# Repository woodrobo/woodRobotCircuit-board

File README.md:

# woodRobotCircuit-board
趣味でロボコン的なロボットを動かす回路を作ろうプロジェクト（？）の回路・基板リポジトリである。ファームウェアは[ここ](https://github.com/woodrobo/woodRobotCircuit-firmware/tree/kanojo_robo)。
ロボコンや趣味のロボット製作等の参考にどうぞ。  

メインボードとモータードライバは2MbpsのRS485で接続されており、プロトコルはwoodRS485という独自規格を用いているが、これも[リポジトリ](https://github.com/woodrobo/wood_rs485)として公開されており、C言語が使用できるマイコンであればどのマイコンでも移植できるよう実装されている。  
モータードライバーは電流制御に対応しており高度な制御が可能となる。  

# 電流制御とは
モーターは一般に抵抗とコイル、そして回転速度に比例する逆起電力の3つが直列接続されたモデルで表現されます。  

$$ Vin = Ri + L\frac{di}{dt}+V$$

電子工作でよく使用されるPWM制御ではこの3つの要素全体にかける電圧を制御しているのでこれは直接的に物理的な意味を持ちません。モーターに流れる電流はトルクに比例すると言われこの電流を制御する電流制御方式ではトルクという物理量を直接的に扱うことができます。

$$ \tau = K_t i $$

製品や研究の世界ではこのトルク制御により運動方程式からモデルを立てて制御をすることが一般となっています。例えばロボティクスでは動力学や逆動力学によりロボットアームを制御しています。モデルに基づいた制御をするために電流制御は必須の機能です。

# 基板の簡単な紹介
woodBoard  
メインボードでありRS485以外にもSPI,I2C,UART,CANなどの通信ポートを備えている。また余った全てのGPIOをピンソケットに出しており、3MbpsのADCモジュールが6つ搭載されているため合計で18Mspsもの高速なAD変換を実現できる。もちろんこれはモジュール数であるのでAD変換可能なピン数はこれより多い。

woodTerminal  
モータードライバー基板などをまとめるための基板であり、1つのターミナル基板につきモータードライバー基板を5枚配置することができる。制御側の電源はRS485ポートの5V電源のほか、DCDCコンバータが搭載されているのでLiPo 3S(11.1V)等からも5Vを生成できる。
  
woodCurrentMD  
初期のモータードライバーであるが、ゲートドライバICが手に入らなかったことや回路トラブルにより闇の基板だぞ。

woodCurrentMD2  
20kHz電流制御モータードライバー。ロジック側とパワー側はフォトカプラで絶縁されており、モーター電流は磁気式の電流センサで計測している。UARTポート、エンコーダポート、ADCポートを搭載しており、また搭載しているマイコンはマルチプレクサにより自由にピン配置を変更できるため拡張性に優れる。180MHz/200MHzデュアルコアマイコンdsPIC33CHにより電流制御とその他処理をコアで分離するためプログラムの拡張性に優れる。  

# 基板発売について  
ここのサイトで基板のみを売ってるぞ！  
https://woodrobo.booth.pm/items/4136212

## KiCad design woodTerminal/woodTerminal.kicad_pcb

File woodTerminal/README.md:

# woodTerminal
モータードライバーなどを5枚までまとめるターミナル基板

仕様
- ロジック側
	- RS485の4ピンポート(A,B,5V,GND)
		- RS485の終端抵抗は横にあるピンヘッダをショートすることで行う
	- 外部電源供給
		- LiPo3S(11.1V)などからDCDCコンバータを通して5Vを供給する(オプション)
	- 電源選択は基板裏面にあるパッドをショートして行う(4ピンコネクタor外部供給)
	- よく考えると外部供給は一度も試してない(ｶｽ)
- パワー側
	- Tコネクタ
  
  # 部品について  
  部品表.csvおよび部品個数表.csvを見てくれ。

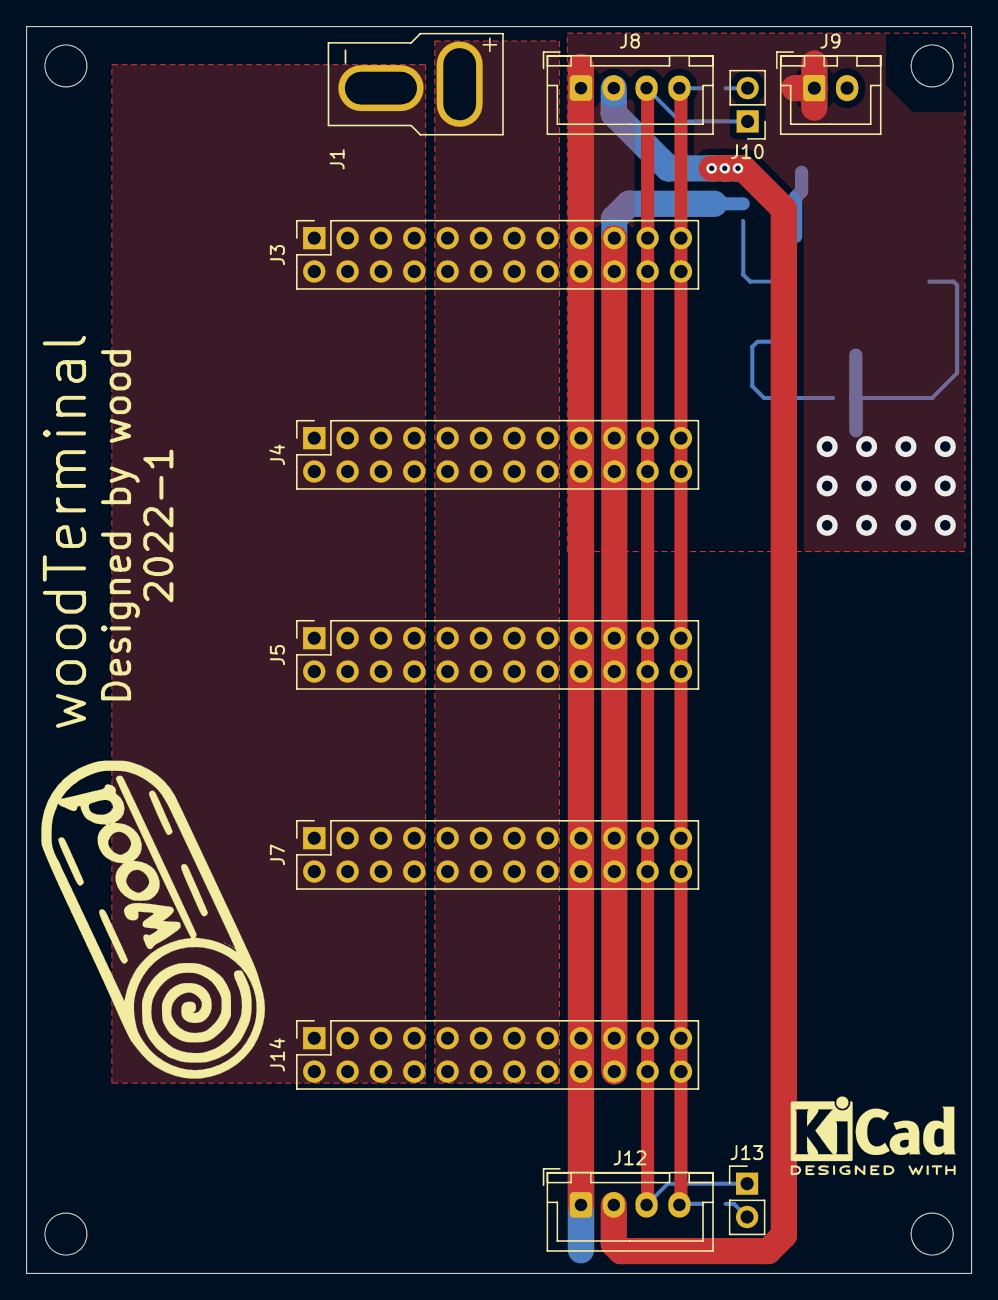
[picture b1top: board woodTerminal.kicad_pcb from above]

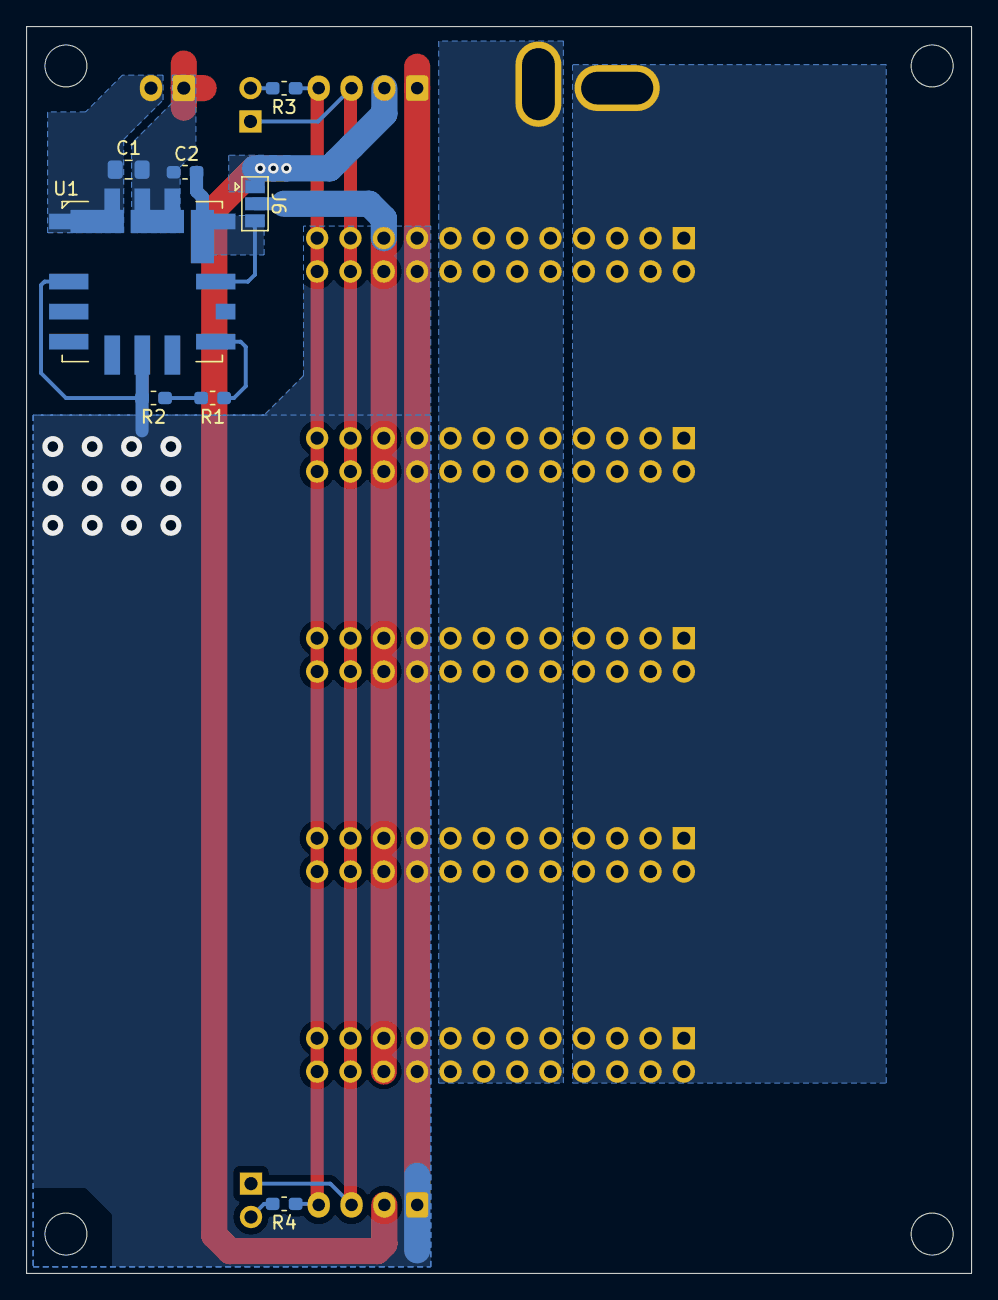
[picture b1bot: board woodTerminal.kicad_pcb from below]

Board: 2 copper layers, 72.0 x 95.0 mm, 23 parts (8 on the bottom side), 13 nets.

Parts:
 : MountingHole_3.2mm_M3
 #2,  #3,  #4: MountingHole_3.2mm_M3
C1: 22u; C_0805_2012Metric_Pad1.15x1.40mm_HandSolder
C2: 10u; C_0603_1608Metric_Pad1.05x0.95mm_HandSolder
J1: Conn_01x02; DeansTConnector_Male
J3, J4, J5, J7, J14: Conn_02x12_Odd_Even; PinSocket_2x12_P2.54mm_Vertical
J6: Conn_01x03; SolderJumper-3_P1.3mm_Open_Pad1.0x1.5mm
J8, J12: Conn_01x04; JST_XH_B4B-XH-A_1x04_P2.50mm_Vertical
J9: Conn_01x02; JST_XH_B2B-XH-A_1x02_P2.50mm_Vertical
J10, J13: Conn_01x02; PinHeader_1x02_P2.54mm_Vertical
R1: 1k; R_0603_1608Metric_Pad1.05x0.95mm_HandSolder
R2: 330; R_0603_1608Metric_Pad1.05x0.95mm_HandSolder
R3, R4: 120; R_0603_1608Metric_Pad1.05x0.95mm_HandSolder
U1: DCDC_Converter_OKL

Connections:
+5V: J3.19, J3.20, J4.19, J4.20, J5.19, J5.20, J6.2, J7.19, J7.20, J14.19, J14.20
+BATT: J1.2, J3.9, J3.10, J3.11, J3.12, J3.13, J3.14, J3.15, J3.16, J4.9, J4.10, J4.11, J4.12, J4.13, J4.14, J4.15, J4.16, J5.9, J5.10, J5.11, J5.12, J5.13, J5.14, J5.15, J5.16, J7.9, J7.10, J7.11, J7.12, J7.13, J7.14, J7.15, J7.16, J14.9, J14.10, J14.11, J14.12, J14.13, J14.14, J14.15, J14.16
/DCDC_OUT: C2.1, J6.3, U1.4, U1.5
/RS485_5V: J6.1, J8.2, J12.2
/RS485_A: J3.23, J3.24, J4.23, J4.24, J5.23, J5.24, J7.23, J7.24, J8.4, J12.4, J14.23, J14.24, R3.1, R4.1
/RS485_B: J3.21, J3.22, J4.21, J4.22, J5.21, J5.22, J7.21, J7.22, J8.3, J10.1, J12.3, J13.1, J14.21, J14.22
GND: C1.2, C2.2, J3.17, J3.18, J4.17, J4.18, J5.17, J5.18, J7.17, J7.18, J8.1, J9.1, J12.1, J14.17, J14.18, R2.2, U1.1, U1.3, U1.7
GNDPWR: J1.1, J3.1, J3.2, J3.3, J3.4, J3.5, J3.6, J3.7, J3.8, J4.1, J4.2, J4.3, J4.4, J4.5, J4.6, J4.7, J4.8, J5.1, J5.2, J5.3, J5.4, J5.5, J5.6, J5.7, J5.8, J7.1, J7.2, J7.3, J7.4, J7.5, J7.6, J7.7, J7.8, J14.1, J14.2, J14.3, J14.4, J14.5, J14.6, J14.7, J14.8
unnamed: J10.2, R3.2
unnamed: J13.2, R4.2
unnamed: R1.1, U1.6
unnamed: R1.2, R2.1
VCC: C1.1, J9.2, U1.2

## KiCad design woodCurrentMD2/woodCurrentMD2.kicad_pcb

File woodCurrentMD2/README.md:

# woodCurrentMD2
2Mbps RS485対応電流制御DCモータードライバー

仕様
- 通信規格2Mbps RS485
	- 受信：電圧制御(PWM値)、電流制御
	- 送信：電流値、AD変換ポートの値、エンコーダのカウント値
- woodTerminal接続端子
	- ロジック側とパワー側は絶縁されている
	- ロジック側：A, B, 5V, GND
	- パワー側　：VCC, GND
	- 詳細はwoodTerminalを参照の事
- 20kHz電流制御
- デバッグUARTポート
	- 現状RXから信号が出てる()
- インクリメンタル型エンコーダポート
	- PICのQEI機能でハードウェア処理
	- たぶん高速な波形も読める
	- Z相はファームウェアが現在対応してない、配線しないこと
- (ポテンショなどの)AD変換ポート

通信規格  
woodRS485で以下のデータをやり取りする。

**マイコンボード→モータードライバー**  
モードは0で電圧制御(PWM値)、1で電流制御を意味する。16bit値は16bitのsigned int型であり、電圧制御ではPWM値(-10000 ~ 10000)を指示し、電流制御では1当たり0.0179[A]となる。  
例えば、電圧制御PWM1000ならば「0,3,232」となる。電流制御1Aならば「1,0,56」(1.0024A)となる。

| バイト数 | データ |
----|---- 
| 1 | モード |
| 2 | 16bit値(上位バイト) |
| 3 | 16bit値(下位バイト) |

**モータードライバー→マイコンボード**  
電流値は16bitのsigned int型であり、1あたり0.0179[A]を意味する。AD変換ポートはAD変換値(12bit 0-4095)が入っている。 エンコーダは16bitのsigned int型である。(インクリメンタル型エンコーダは差分しか意味を持たないのでunsignedと解釈してもsignedと解釈しても同じ)

| バイト数 | データ |
----|---- 
| 1 | 電流値(上位バイト) |
| 2 | 電流値(下位バイト) |
| 3 | AD変換ポート(上位バイト) |
| 4 | AD変換ポート(下位バイト) |
| 5 | エンコーダ(上位バイト) |
| 6 | エンコーダ(下位バイト) |
  
  # 部品について  
  部品表.csvおよび部品個数表.csvを見てくれ。

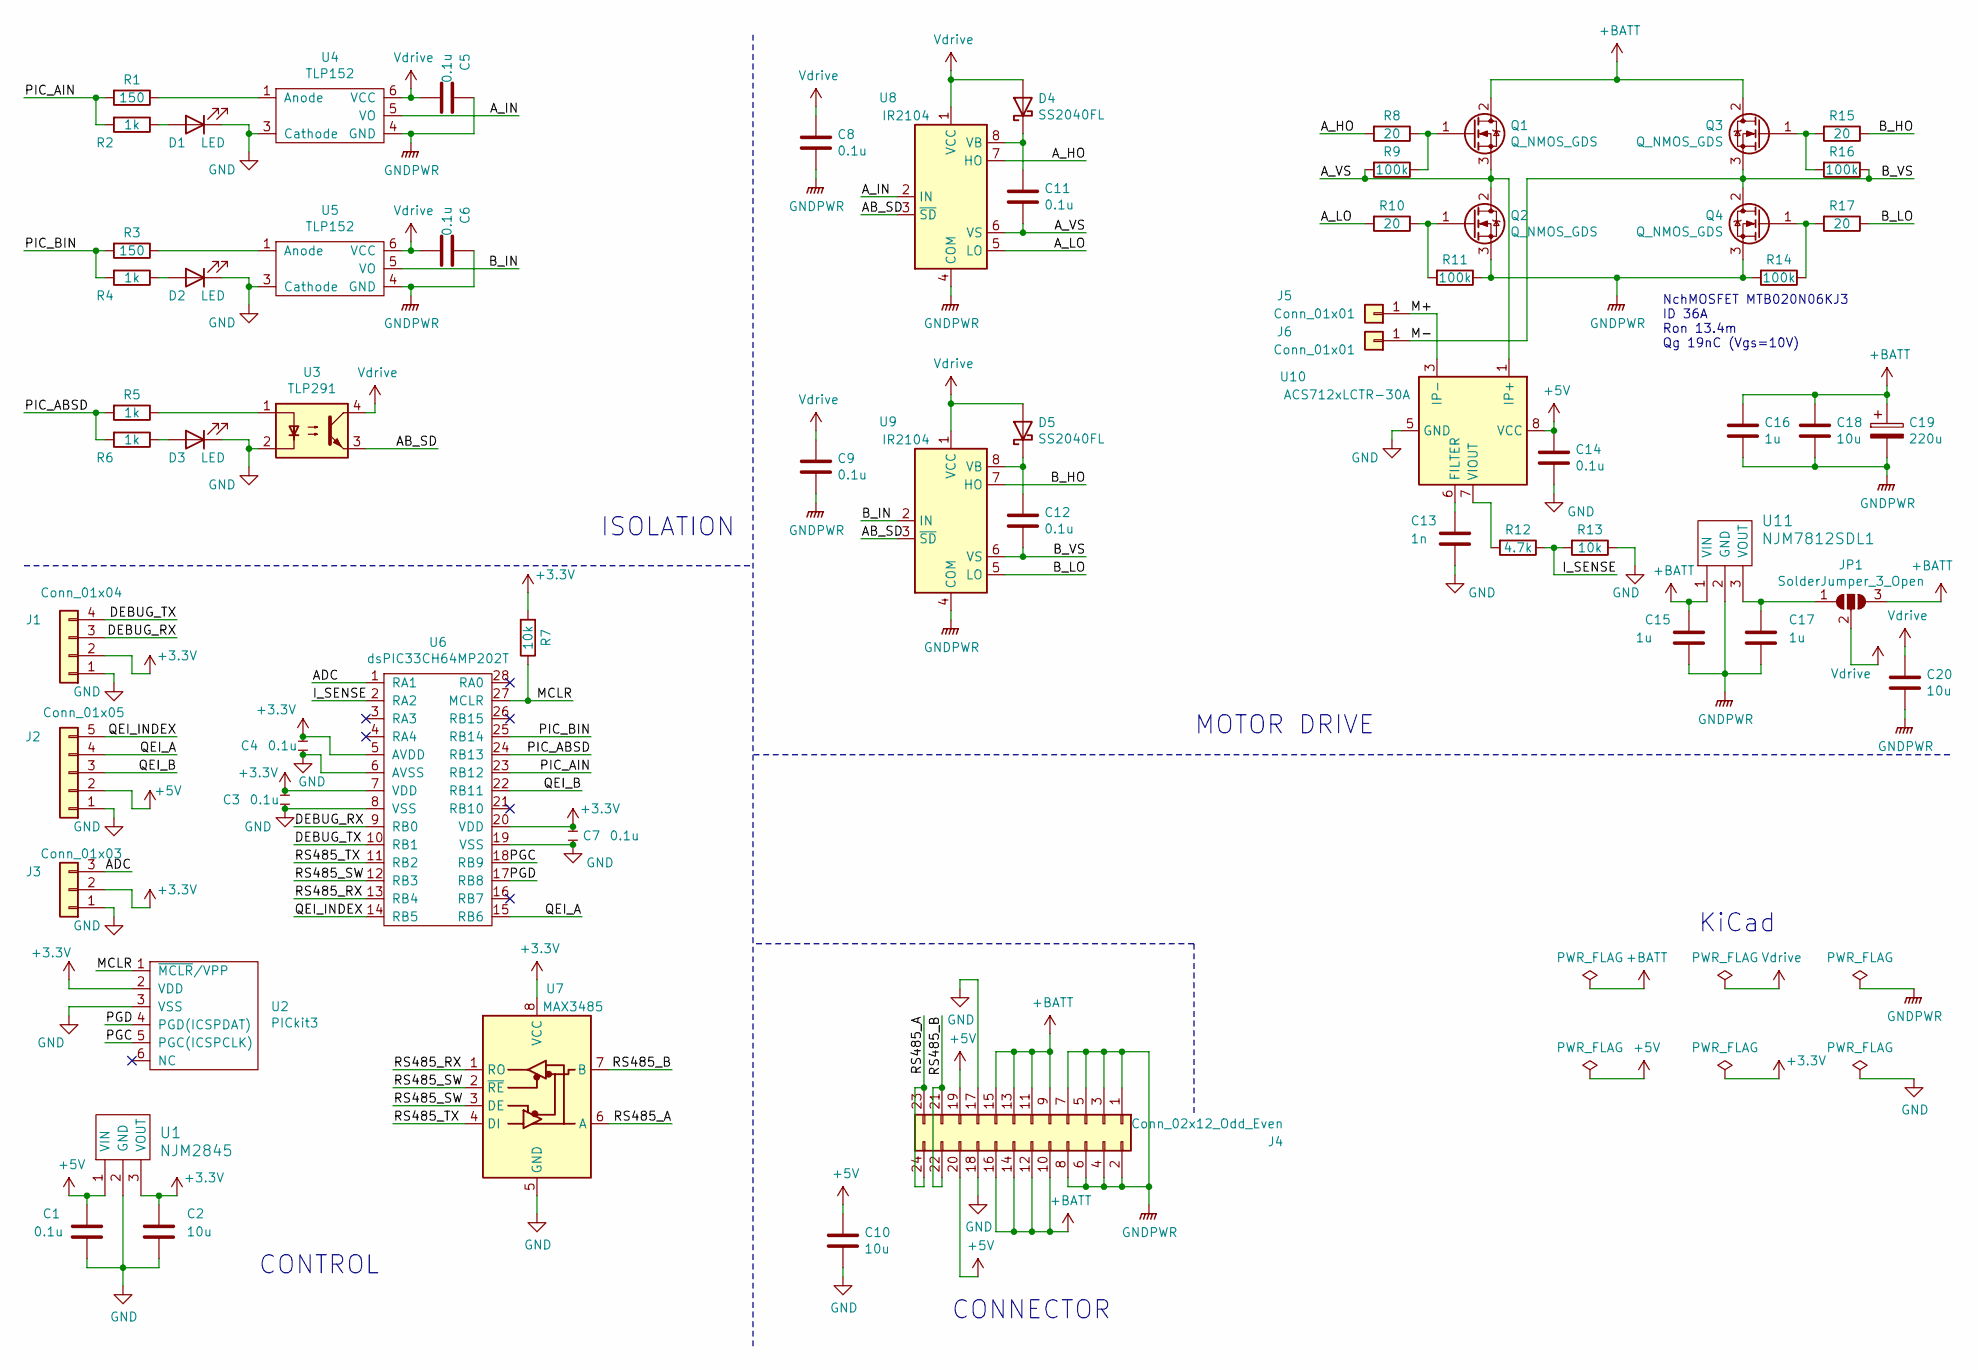
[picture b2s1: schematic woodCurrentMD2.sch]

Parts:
C1, C3, C4, C5, C6, C7, C8, C9, C11, C12, C14: 0.1u; C_0603_1608Metric
C2, C10, C18, C20: 10u; C_0603_1608Metric
C13: 1n; C_0603_1608Metric
C15, C16, C17: 1u; C_0603_1608Metric
C19: 220u; CP_Elec_10x10
D1, D2, D3: LED; LED_0603_1608Metric
D4, D5: SS2040FL; D_1206_3216Metric
J1: Conn_01x04; JST_XH_S4B-XH-A_1x04_P2.50mm_Horizontal
J2: Conn_01x05; JST_XH_S5B-XH-A_1x05_P2.50mm_Horizontal
J3: Conn_01x03; JST_XH_S3B-XH-A_1x03_P2.50mm_Horizontal
J4: Conn_02x12_Odd_Even; PinHeader_2x12_P2.54mm_Vertical
J5, J6: Conn_01x01; MountingHole_2.2mm_M2_Pad
JP1: SolderJumper_3_Open; SolderJumper-3_P1.3mm_Open_RoundedPad1.0x1.5mm_NumberLabels
Q1, Q2, Q3, Q4: Q_NMOS_GDS; TO-252-2
R1, R3: 150; R_0603_1608Metric
R2, R4, R5, R6: 1k; R_0603_1608Metric
R7, R13: 10k; R_0603_1608Metric
R8, R10, R15, R17: 20; R_0603_1608Metric
R9, R11, R14, R16: 100k; R_0603_1608Metric
R12: 4.7k; R_0603_1608Metric
U1: NJM2845; TO-252-2
U2: PICkit3; PinHeader_1x06_P2.54mm_Horizontal
U3: TLP291; SOIC-4_4.55x2.6mm_P1.27mm
U4, U5: TLP152; SO-6_4.4x3.6mm_P1.27mm
U6: dsPIC33CH64MP202T; SSOP-28_5.3x10.2mm_P0.65mm
U7: MAX3485; SOIC-8_3.9x4.9mm_P1.27mm
U8, U9: IR2104; SOIC-8_3.9x4.9mm_P1.27mm
U10: ACS712xLCTR-30A; SOIC-8_3.9x4.9mm_P1.27mm
U11: NJM7812SDL1; TO-252-2

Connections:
+3V3: C2.1, C3.1, C4.1, C7.1, J1.2, J3.2, R7.2, U1.3 (VOUT), U2.2 (VDD), U6.5 (AVDD), U6.7 (VDD), U6.20 (VDD), U7.8 (VCC)
+5V: C1.1, C10.1, C14.1, J2.2, J4.19, J4.20, U1.1 (VIN), U10.8 (VCC)
+BATT: C15.1, C16.1, C18.1, C19.1, J4.9, J4.10, J4.11, J4.12, J4.13, J4.14, J4.15, J4.16, JP1.3 (B), Q1.2 (D), Q3.2 (D), U11.1 (VIN)
/AB_SD: U3.3, U8.3 (~SD), U9.3 (~SD)
/ADC: J3.3, U6.1 (RA1)
/A_HO: R8.2, U8.7 (HO)
/A_IN: U4.5 (VO), U8.2 (IN)
/A_LO: R10.2, U8.5 (LO)
/A_VS: C11.2, Q1.3 (S), Q2.2 (D), R9.2, U8.6 (VS), U10.1 (IP+), U10.2 (IP+)
/B_HO: R15.1, U9.7 (HO)
/B_IN: U5.5 (VO), U9.2 (IN)
/B_LO: R17.1, U9.5 (LO)
/B_VS: C12.2, J6.1, Q3.3 (S), Q4.2 (D), R16.1, U9.6 (VS)
/DEBUG_RX: J1.3, U6.9 (RB0)
/DEBUG_TX: J1.4, U6.10 (RB1)
/I_SENSE: R12.1, R13.2, U6.2 (RA2)
/M+: J5.1, U10.3 (IP-), U10.4 (IP-)
/MCLR: R7.1, U2.1 (~MCLR~/VPP), U6.27 (MCLR)
/PGC: U2.5 (PGC(ICSPCLK)), U6.18 (RB9)
/PGD: U2.4 (PGD(ICSPDAT)), U6.17 (RB8)
/PIC_ABSD: R5.2, R6.2, U6.24 (RB13)
/PIC_AIN: R1.2, R2.2, U6.23 (RB12)
/PIC_BIN: R3.2, R4.2, U6.25 (RB14)
/QEI_A: J2.4, U6.15 (RB6)
/QEI_B: J2.3, U6.22 (RB11)
/QEI_INDEX: J2.5, U6.14 (RB5)
/RS485_A: J4.23, J4.24, U7.6 (A)
/RS485_B: J4.21, J4.22, U7.7 (B)
/RS485_RX: U6.13 (RB4), U7.1 (RO)
/RS485_SW: U6.12 (RB3), U7.2 (~RE), U7.3 (DE)
/RS485_TX: U6.11 (RB2), U7.4 (DI)
GND: C1.2, C2.2, C3.2, C4.2, C7.2, C10.2, C13.2, C14.2, D1.1 (K), D2.1 (K), D3.1 (K), J1.1, J2.1, J3.1, J4.17, J4.18, R13.1, U1.2 (GND), U2.3 (VSS), U3.2, U4.3 (Cathode), U5.3 (Cathode), U6.6 (AVSS), U6.8 (VSS), U6.19 (VSS), U7.5 (GND), U10.5 (GND)
GNDPWR: C5.1, C6.1, C8.2, C9.2, C15.2, C16.2, C17.2, C18.2, C19.2, C20.2, J4.1, J4.2, J4.3, J4.4, J4.5, J4.6, J4.7, J4.8, Q2.3 (S), Q4.3 (S), R11.1, R14.2, U4.4 (GND), U5.4 (GND), U8.4 (COM), U9.4 (COM), U11.2 (GND)
unnamed: C11.1, D4.1 (K), U8.8 (VB)
unnamed: C12.1, D5.1 (K), U9.8 (VB)
unnamed: C13.1, U10.6 (FILTER)
unnamed: C17.1, JP1.1 (A), U11.3 (VOUT)
unnamed: D1.2 (A), R2.1
unnamed: D2.2 (A), R4.1
unnamed: D3.2 (A), R6.1
unnamed: Q1.1 (G), R8.1, R9.1
unnamed: Q2.1 (G), R10.1, R11.2
unnamed: Q3.1 (G), R15.2, R16.2
unnamed: Q4.1 (G), R14.1, R17.2
unnamed: R1.1, U4.1 (Anode)
unnamed: R3.1, U5.1 (Anode)
unnamed: R5.1, U3.1
unnamed: R12.2, U10.7 (VIOUT)
Vdrive: C5.2, C6.2, C8.1, C9.1, C20.1, D4.2 (A), D5.2 (A), JP1.2 (C), U3.4, U4.6 (VCC), U5.6 (VCC), U8.1 (VCC), U9.1 (VCC)

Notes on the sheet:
CONTROL
ISOLATION
CONNECTOR
KiCad
MOTOR DRIVE
NchMOSFET MTB020N06KJ3 ID 36A Ron 13.4m Qg 19nC (Vgs=10V)

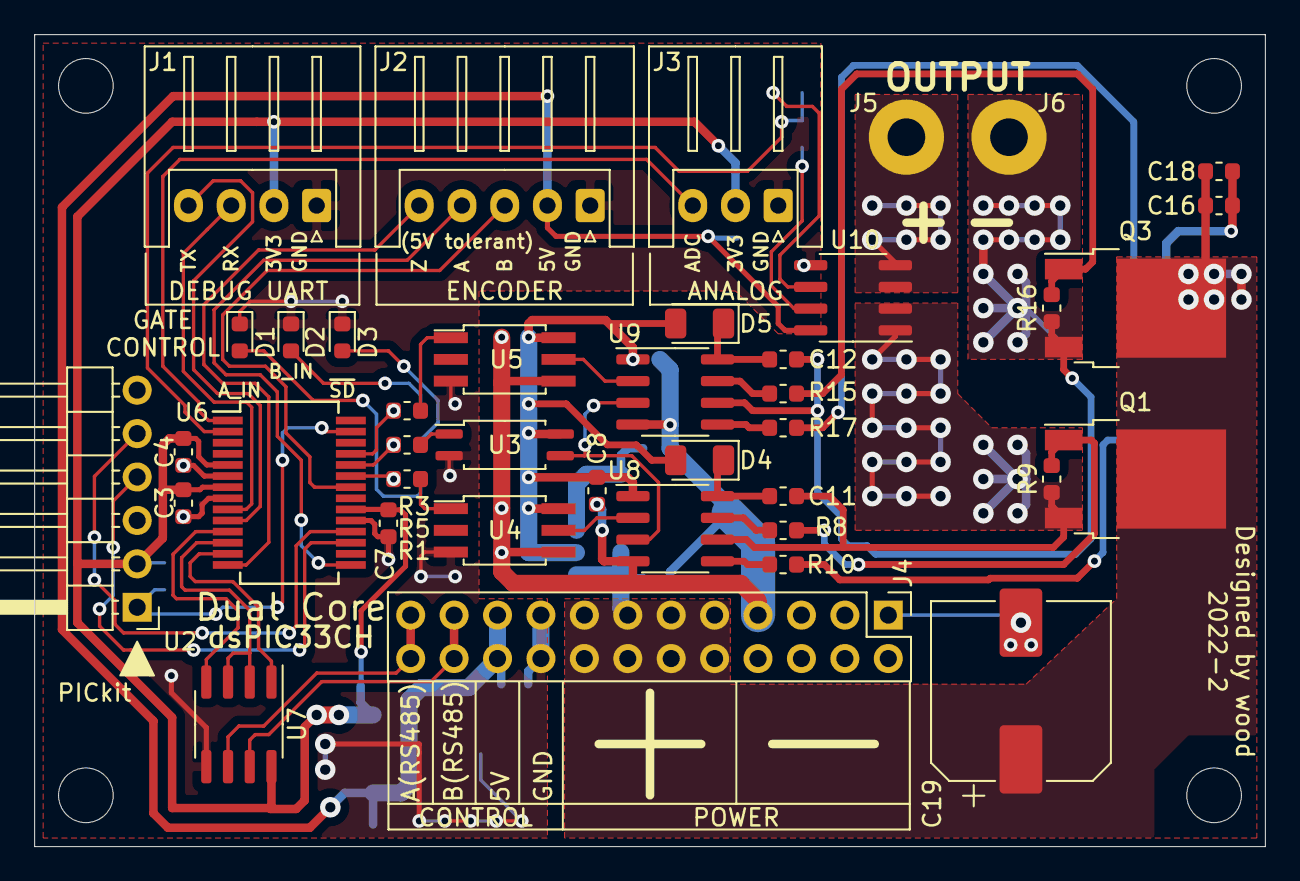
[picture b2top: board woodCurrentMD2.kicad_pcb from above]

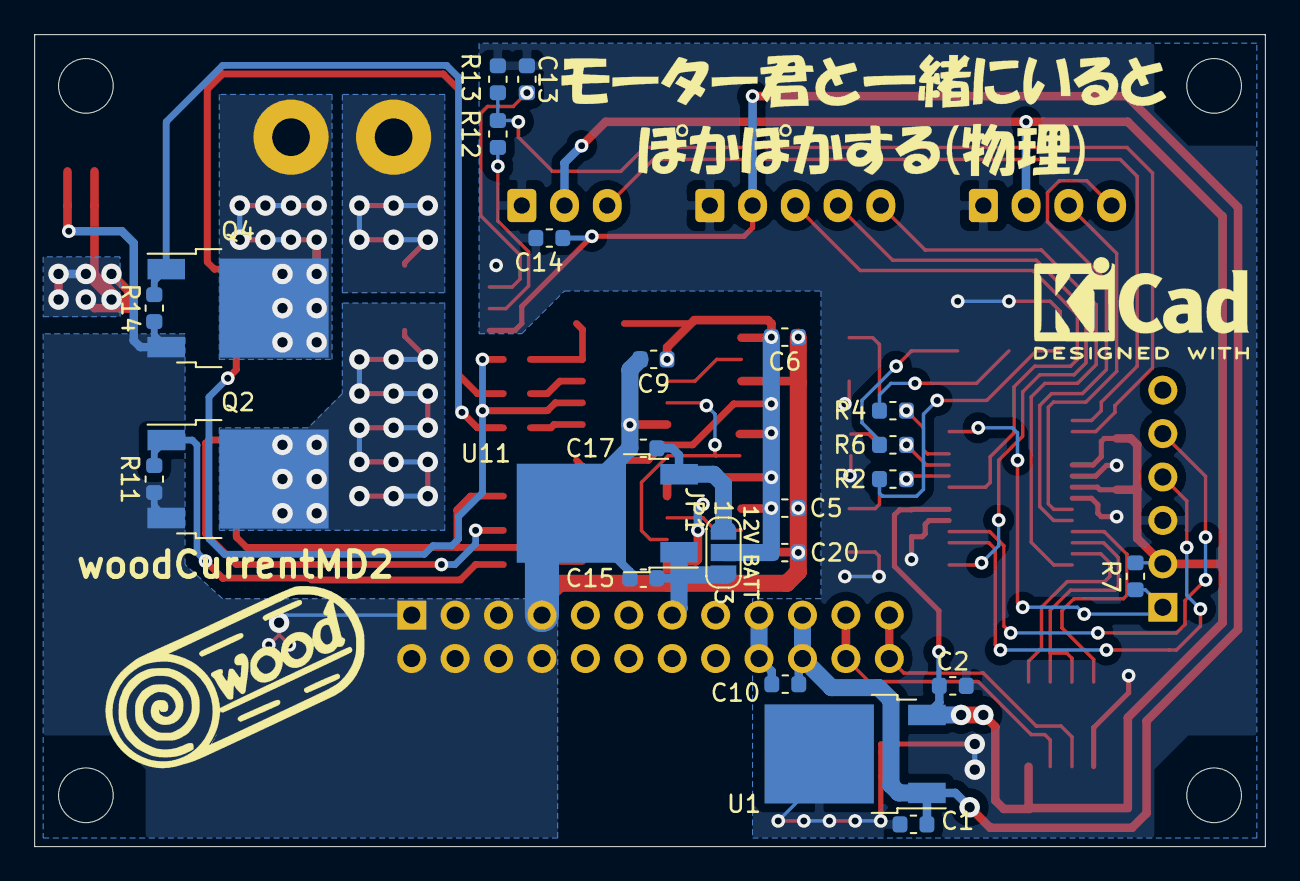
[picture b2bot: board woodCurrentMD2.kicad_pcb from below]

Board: 2 copper layers, 72.0 x 47.5 mm, 68 parts (24 on the bottom side), 49 nets.

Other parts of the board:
 : MountingHole_3.2mm_M3
 #2,  #3,  #4: MountingHole_3.2mm_M3

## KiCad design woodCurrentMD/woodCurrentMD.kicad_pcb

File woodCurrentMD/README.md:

# woodCurrentMD
電流制御モタドラを作ろうとした。  
後継プロジェクトはwoodCurrentMD2なので、そちらをご覧ください。

仕様
- PWMをフォトカプラに入れるとFETから煙が出る
- フルブリッジドライバのA3921が手に入らない

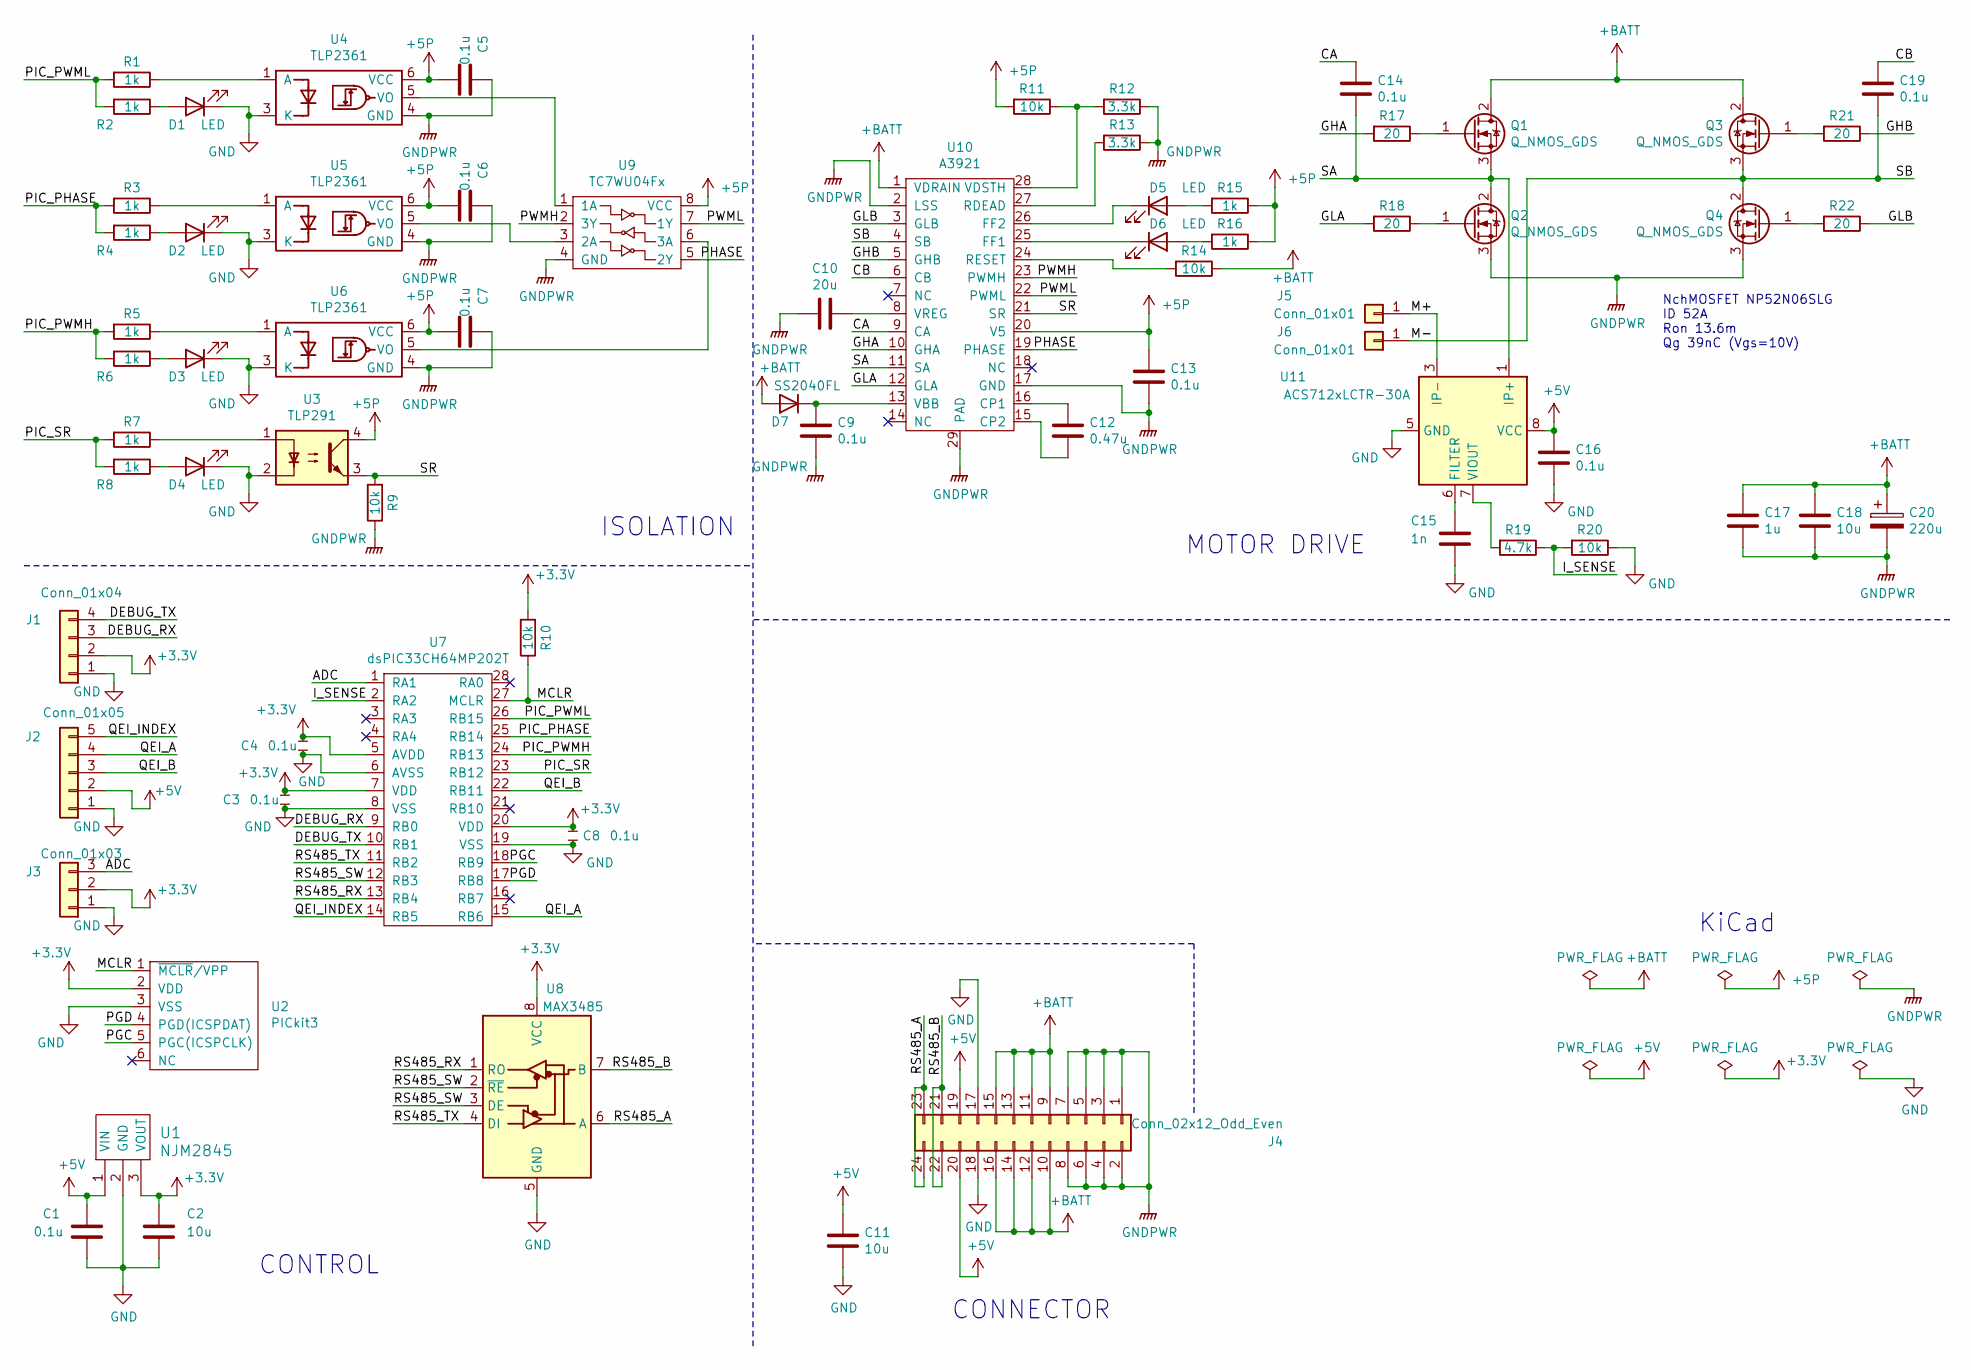
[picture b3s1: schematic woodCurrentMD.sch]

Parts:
C1, C3, C4, C5, C6, C7, C8, C9, C13, C14, C16, C19: 0.1u; C_0603_1608Metric
C2, C11, C18: 10u; C_0603_1608Metric
C10: 20u; C_0805_2012Metric
C12: 0.47u; C_0603_1608Metric
C15: 1n; C_0603_1608Metric
C17: 1u; C_0603_1608Metric
C20: 220u; CP_Elec_10x10
D1, D2, D3, D4, D5, D6: LED; LED_0603_1608Metric
D7: SS2040FL; D_1206_3216Metric
J1: Conn_01x04; JST_XH_S4B-XH-A_1x04_P2.50mm_Horizontal
J2: Conn_01x05; JST_XH_S5B-XH-A_1x05_P2.50mm_Horizontal
J3: Conn_01x03; JST_XH_S3B-XH-A_1x03_P2.50mm_Horizontal
J4: Conn_02x12_Odd_Even; PinHeader_2x12_P2.54mm_Vertical
J5, J6: Conn_01x01; MountingHole_2.2mm_M2_Pad
Q1, Q2, Q3, Q4: Q_NMOS_GDS; TO-252-2
R1, R2, R3, R4, R5, R6, R7, R8, R15, R16: 1k; R_0603_1608Metric
R9, R10, R11, R14, R20: 10k; R_0603_1608Metric
R12, R13: 3.3k; R_0603_1608Metric
R17, R18, R21, R22: 20; R_0603_1608Metric
R19: 4.7k; R_0603_1608Metric
U1: NJM2845; TO-252-2
U2: PICkit3; PinHeader_1x06_P2.54mm_Horizontal
U3: TLP291; SOIC-4_4.55x2.6mm_P1.27mm
U4, U5, U6: TLP2361; SO-6_4.4x3.6mm_P1.27mm
U7: dsPIC33CH64MP202T; SSOP-28_5.3x10.2mm_P0.65mm
U8: MAX3485; SOIC-8_3.9x4.9mm_P1.27mm
U9: TC7WU04Fx; SSOP-8_2.95x2.8mm_P0.65mm
U10: A3921; HTSSOP-28-1EP_4.4x9.7mm_P0.65mm_EP2.85x5.4mm
U11: ACS712xLCTR-30A; SOIC-8_3.9x4.9mm_P1.27mm

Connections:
+3V3: C2.1, C3.1, C4.1, C8.1, J1.2, J3.2, R10.2, U1.3 (VOUT), U2.2 (VDD), U7.5 (AVDD), U7.7 (VDD), U7.20 (VDD), U8.8 (VCC)
+5P: C5.2, C6.2, C7.2, C13.1, R11.2, R15.1, R16.1, U3.4, U4.6 (VCC), U5.6 (VCC), U6.6 (VCC), U9.8 (VCC), U10.20 (V5)
+5V: C1.1, C11.1, C16.1, J2.2, J4.19, J4.20, U1.1 (VIN), U11.8 (VCC)
+BATT: C17.1, C18.1, C20.1, D7.2 (A), J4.9, J4.10, J4.11, J4.12, J4.13, J4.14, J4.15, J4.16, Q1.2 (D), Q3.2 (D), R14.1, U10.1 (VDRAIN)
/ADC: J3.3, U7.1 (RA1)
/CA: C14.1, U10.9 (CA)
/CB: C19.1, U10.6 (CB)
/DEBUG_RX: J1.3, U7.9 (RB0)
/DEBUG_TX: J1.4, U7.10 (RB1)
/GHA: R17.2, U10.10 (GHA)
/GHB: R21.1, U10.5 (GHB)
/GLA: R18.2, U10.12 (GLA)
/GLB: R22.1, U10.3 (GLB)
/I_SENSE: R19.1, R20.2, U7.2 (RA2)
/M+: J5.1, U11.3 (IP-), U11.4 (IP-)
/M-: C19.2, J6.1, Q3.3 (S), Q4.2 (D), U10.4 (SB)
/MCLR: R10.1, U2.1 (~MCLR~/VPP), U7.27 (MCLR)
/PGC: U2.5 (PGC(ICSPCLK)), U7.18 (RB9)
/PGD: U2.4 (PGD(ICSPDAT)), U7.17 (RB8)
/PHASE: U9.5 (2Y), U10.19 (PHASE)
/PIC_PHASE: R3.2, R4.2, U7.25 (RB14)
/PIC_PWMH: R5.2, R6.2, U7.24 (RB13)
/PIC_PWML: R1.2, R2.2, U7.26 (RB15)
/PIC_SR: R7.2, R8.2, U7.23 (RB12)
/PWMH: U9.2 (3Y), U10.23 (PWMH)
/PWML: U9.7 (1Y), U10.22 (PWML)
/QEI_A: J2.4, U7.15 (RB6)
/QEI_B: J2.3, U7.22 (RB11)
/QEI_INDEX: J2.5, U7.14 (RB5)
/RS485_A: J4.23, J4.24, U8.6 (A)
/RS485_B: J4.21, J4.22, U8.7 (B)
/RS485_RX: U7.13 (RB4), U8.1 (RO)
/RS485_SW: U7.12 (RB3), U8.2 (~RE), U8.3 (DE)
/RS485_TX: U7.11 (RB2), U8.4 (DI)
/SA: C14.2, Q1.3 (S), Q2.2 (D), U10.11 (SA), U11.1 (IP+), U11.2 (IP+)
/SR: R9.2, U3.3, U10.21 (SR)
GND: C1.2, C2.2, C3.2, C4.2, C8.2, C11.2, C15.2, C16.2, D1.1 (K), D2.1 (K), D3.1 (K), D4.1 (K), J1.1, J2.1, J3.1, J4.17, J4.18, R20.1, U1.2 (GND), U2.3 (VSS), U3.2, U4.3 (K), U5.3 (K), U6.3 (K), U7.6 (AVSS), U7.8 (VSS), U7.19 (VSS), U8.5 (GND), U11.5 (GND)
GNDPWR: C5.1, C6.1, C7.1, C9.2, C10.2, C13.2, C17.2, C18.2, C20.2, J4.1, J4.2, J4.3, J4.4, J4.5, J4.6, J4.7, J4.8, Q2.3 (S), Q4.3 (S), R9.1, R12.1, R13.1, U4.4 (GND), U5.4 (GND), U6.4 (GND), U9.4 (GND), U10.2 (LSS), U10.17 (GND), U10.29 (PAD)
unnamed: C9.1, D7.1 (K), U10.13 (VBB)
unnamed: C10.1, U10.8 (VREG)
unnamed: C12.1, U10.16 (CP1)
unnamed: C12.2, U10.15 (CP2)
unnamed: C15.1, U11.6 (FILTER)
unnamed: D1.2 (A), R2.1
unnamed: D2.2 (A), R4.1
unnamed: D3.2 (A), R6.1
unnamed: D4.2 (A), R8.1
unnamed: D5.1 (K), U10.26 (FF2)
unnamed: D5.2 (A), R15.2
unnamed: D6.1 (K), U10.25 (FF1)
unnamed: D6.2 (A), R16.2
unnamed: Q1.1 (G), R17.1
unnamed: Q2.1 (G), R18.1
unnamed: Q3.1 (G), R21.2
unnamed: Q4.1 (G), R22.2
unnamed: R1.1, U4.1 (A)
unnamed: R3.1, U5.1 (A)
unnamed: R5.1, U6.1 (A)
unnamed: R7.1, U3.1
unnamed: R11.1, R12.2, U10.28 (VDSTH)
unnamed: R13.2, U10.27 (RDEAD)
unnamed: R14.2, U10.24 (RESET)
unnamed: R19.2, U11.7 (VIOUT)
unnamed: U4.5 (VO), U9.1 (1A)
unnamed: U5.5 (VO), U9.3 (2A)
unnamed: U6.5 (VO), U9.6 (3A)

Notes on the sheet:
NchMOSFET NP52N06SLG ID 52A Ron 13.6m Qg 39nC (Vgs=10V)
CONTROL
ISOLATION
CONNECTOR
KiCad
MOTOR DRIVE

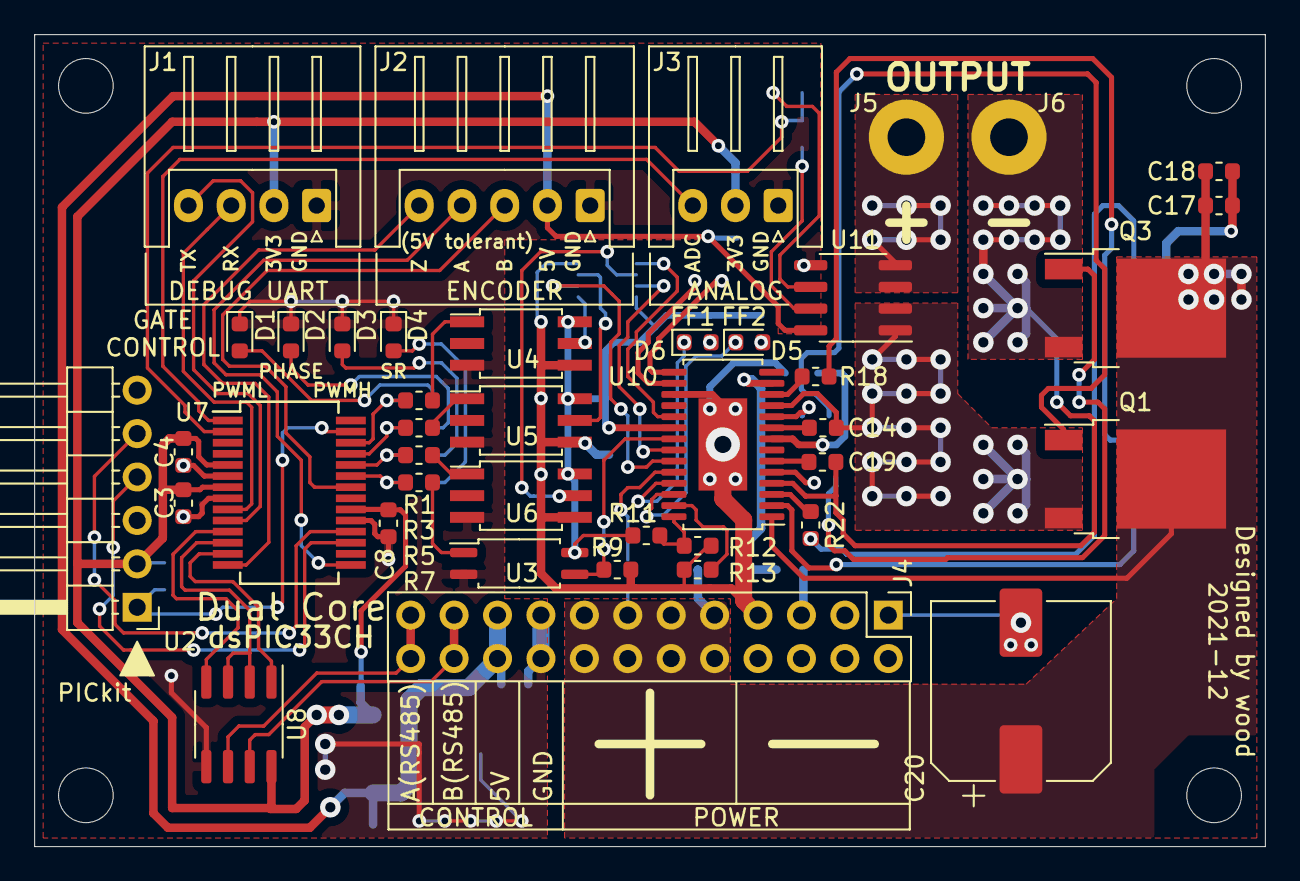
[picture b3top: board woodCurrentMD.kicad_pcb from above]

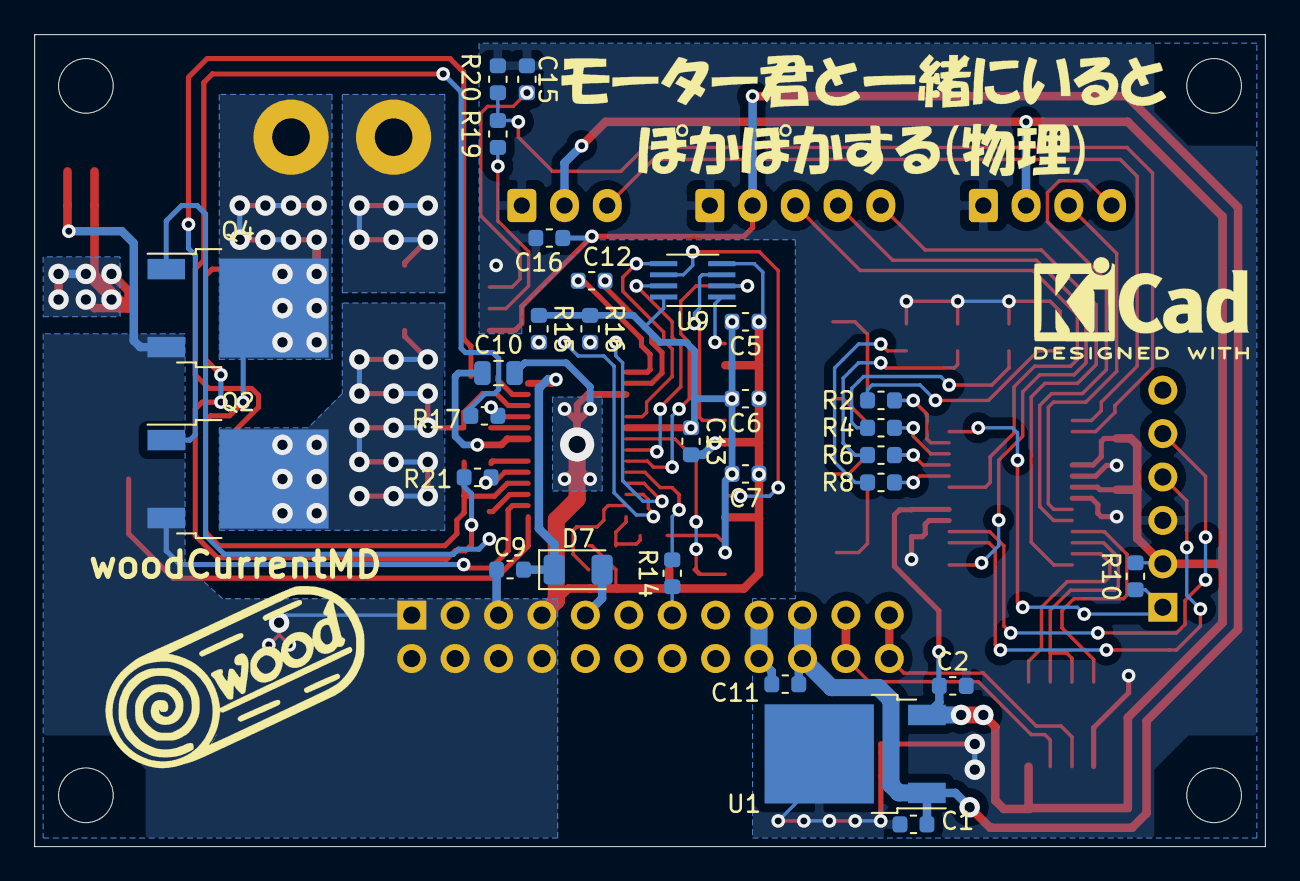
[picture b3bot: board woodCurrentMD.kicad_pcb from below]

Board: 2 copper layers, 72.0 x 47.5 mm, 74 parts (29 on the bottom side), 66 nets.

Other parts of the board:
 : MountingHole_3.2mm_M3
 #2,  #3,  #4: MountingHole_3.2mm_M3
